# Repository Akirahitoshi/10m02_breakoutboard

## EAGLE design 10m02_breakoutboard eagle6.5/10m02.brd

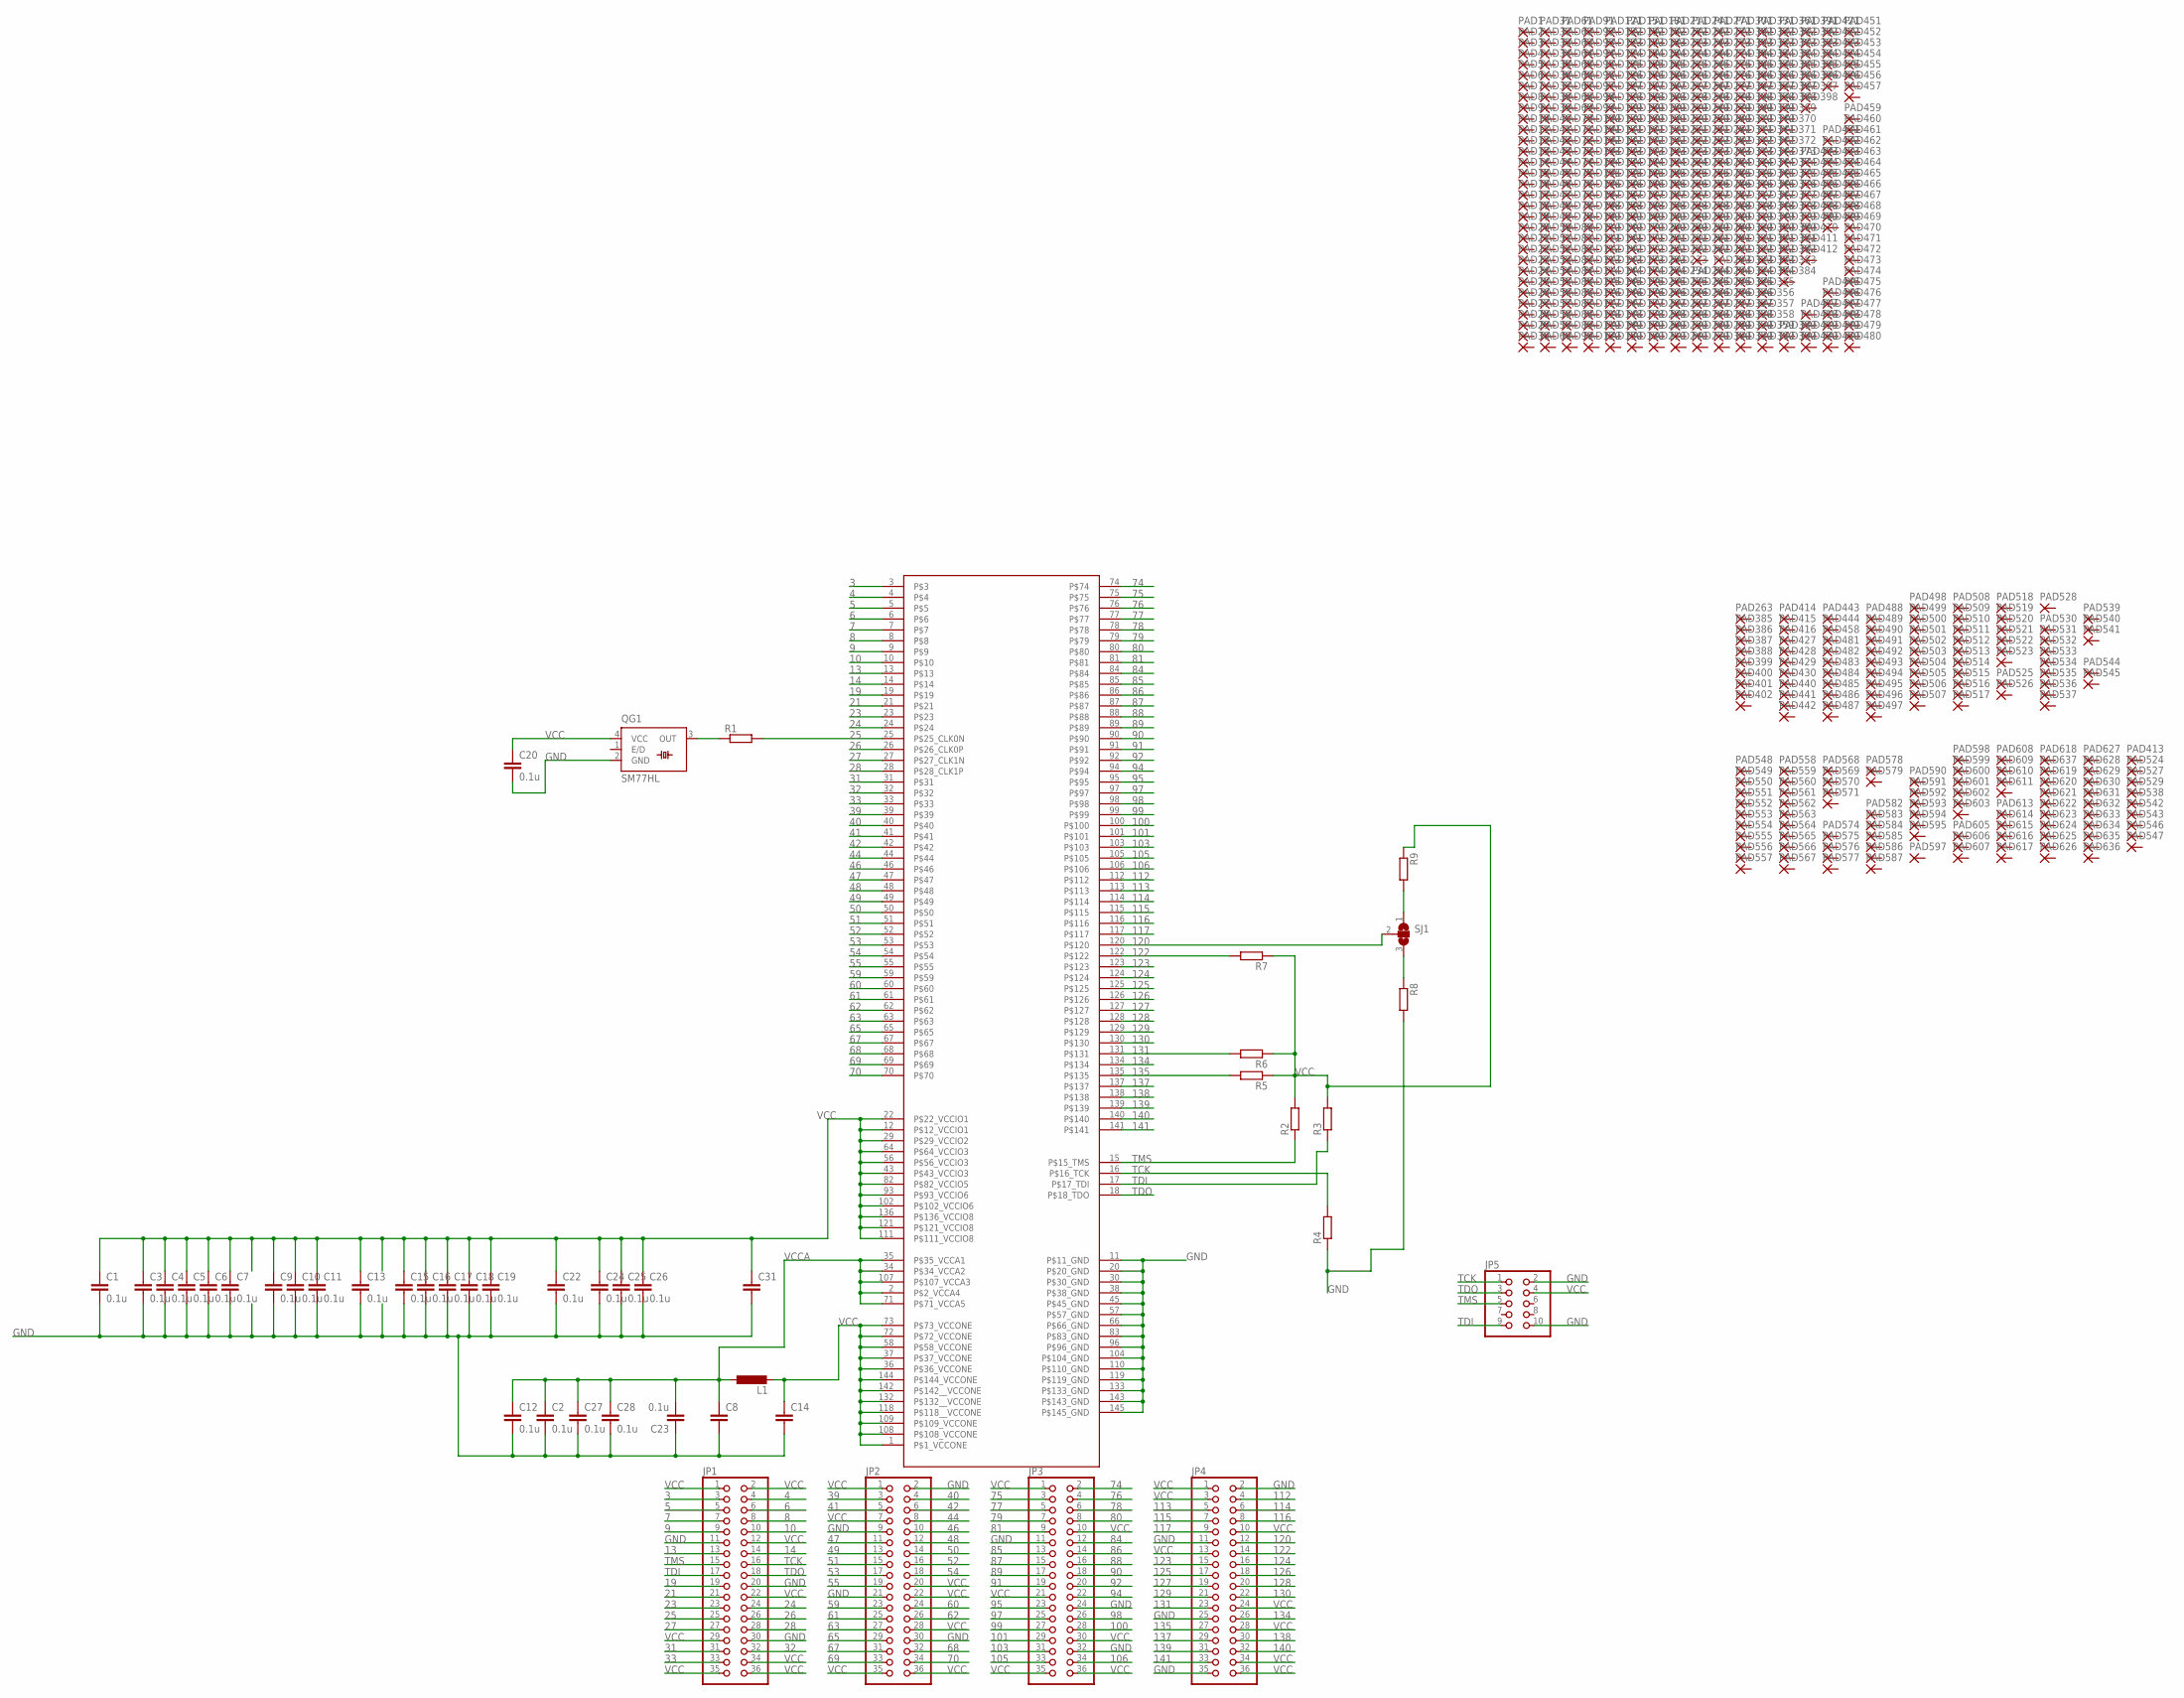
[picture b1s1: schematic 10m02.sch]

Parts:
C1, C2, C3, C4, C5, C6, C7, C9, C10, C11, C12, C13, C15, C16, C17, C18, C19, C20, C22, C23, C24, C25, C26, C27, C28: 0.1u; C0603K
C8, C14: C-EUC3216; C3216
C31: C-EUC3225; C3225
IC1: 10M02SC144; TQFP144G
JP1, JP2, JP3, JP4: PINHD-2X18; 2X18
JP5: PINHD-2X5; 2X05
L1: L-EUL3216C; L3216C
PAD1, PAD2, PAD3, PAD4, PAD5, PAD6, PAD7, PAD8, PAD9, PAD10, PAD11, PAD12, PAD13, PAD14, PAD15, PAD16, PAD17, PAD18, PAD19, PAD20, PAD21, PAD22, PAD23, PAD24, PAD25, PAD26, PAD27, PAD28, PAD29, PAD30, PAD31, PAD32, PAD33, PAD34, PAD35, PAD36, PAD37, PAD38, PAD39, PAD40, PAD41, PAD42, PAD43, PAD44, PAD45, PAD46, PAD47, PAD48, PAD49, PAD50, PAD51, PAD52, PAD53, PAD54, PAD55, PAD56, PAD57, PAD58, PAD59, PAD60, PAD61, PAD62, PAD63, PAD64, PAD65, PAD66, PAD67, PAD68, PAD69, PAD70, PAD71, PAD72, PAD73, PAD74, PAD75, PAD76, PAD77, PAD78, PAD79, PAD80, PAD81, PAD82, PAD83, PAD84, PAD85, PAD86, PAD87, PAD88, PAD89, PAD90, PAD91, PAD92, PAD93, PAD94, PAD95, PAD96, PAD97, PAD98, PAD99, PAD100, PAD101, PAD102, PAD103, PAD104, PAD105, PAD106, PAD107, PAD108, PAD109, PAD110, PAD111, PAD112, PAD113, PAD114, PAD115, PAD116, PAD117, PAD118, PAD119, PAD120, PAD121, PAD122, PAD123, PAD124, PAD125, PAD126, PAD127, PAD128, PAD129, PAD130, PAD131, PAD132, PAD133, PAD134, PAD135, PAD136, PAD137, PAD138, PAD139, PAD140, PAD141, PAD142, PAD143, PAD144, PAD145, PAD146, PAD147, PAD148, PAD149, PAD150, PAD151, PAD152, PAD153, PAD154, PAD155, PAD156, PAD157, PAD158, PAD159, PAD160, PAD161, PAD162, PAD163, PAD164, PAD165, PAD166, PAD167, PAD168, PAD169, PAD170, PAD171, PAD172, PAD173, PAD174, PAD175, PAD176, PAD177, PAD178, PAD179, PAD180, PAD181, PAD182, PAD183, PAD184, PAD185, PAD186, PAD187, PAD188, PAD189, PAD190, PAD191, PAD192, PAD193, PAD194, PAD195, PAD196, PAD197, PAD198, PAD199, PAD200, PAD201, PAD202, PAD203, PAD204, PAD205, PAD206, PAD207, PAD208, PAD209, PAD210, PAD211, PAD212, PAD213, PAD214, PAD215, PAD216, PAD217, PAD218, PAD219, PAD220, PAD221, PAD222, PAD223, PAD224, PAD225, PAD226, PAD227, PAD228, PAD229, PAD230, PAD231, PAD232, PAD233, PAD234, PAD235, PAD236, PAD237, PAD238, PAD239, PAD240, PAD241, PAD242, PAD243, PAD244, PAD245, PAD246, PAD247, PAD248, PAD249, PAD250, PAD251, PAD252, PAD253, PAD254, PAD255, PAD256, PAD257, PAD258, PAD259, PAD260, PAD261, PAD262, PAD264, PAD265, PAD266, PAD267, PAD268, PAD269, PAD270, PAD271, PAD272, PAD273, PAD274, PAD275, PAD276, PAD277, PAD278, PAD279, PAD280, PAD281, PAD282, PAD283, PAD284, PAD285, PAD286, PAD287, PAD288, PAD289, PAD290, PAD291, PAD292, PAD293, PAD294, PAD295, PAD296, PAD297, PAD298, PAD299, PAD300, PAD301, PAD302, PAD303, PAD304, PAD305, PAD306, PAD307, PAD308, PAD309, PAD310, PAD311, PAD312, PAD313, PAD314, PAD315, PAD316, PAD317, PAD318, PAD319, PAD320, PAD321, PAD322, PAD323, PAD324, PAD325, PAD326, PAD327, PAD328, PAD329, PAD330, PAD331, PAD332, PAD333, PAD334, PAD335, PAD336, PAD337, PAD338, PAD339, PAD340, PAD341, PAD342, PAD343, PAD344, PAD345, PAD346, PAD347, PAD348, PAD349, PAD350, PAD351, PAD352, PAD353, PAD354, PAD355, PAD356, PAD357, PAD358, PAD359, PAD360, PAD361, PAD362, PAD363, PAD364, PAD365, PAD366, PAD367, PAD368, PAD369, PAD370, PAD371, PAD372, PAD373, PAD374, PAD375, PAD376, PAD377, PAD378, PAD379, PAD380, PAD381, PAD382, PAD383, PAD384, PAD389, PAD390, PAD391, PAD392, PAD393, PAD394, PAD395, PAD396, PAD397, PAD398, PAD403, PAD404, PAD405, PAD406, PAD407, PAD408, PAD409, PAD410, PAD411, PAD412, PAD417, PAD418, PAD419, PAD420, PAD421, PAD422, PAD423, PAD424, PAD425, PAD426, PAD431, PAD432, PAD433, PAD434, PAD435, PAD436, PAD437, PAD438, PAD439, PAD445, PAD446, PAD447, PAD448, PAD449, PAD450, PAD451, PAD452, PAD453, PAD454, PAD455, PAD456, PAD457, PAD459, PAD460, PAD461, PAD462, PAD463, PAD464, PAD465, PAD466, PAD467, PAD468, PAD469, PAD470, PAD471, PAD472, PAD473, PAD474, PAD475, PAD476, PAD477, PAD478, PAD479, PAD480: 1,6/0,9
PAD263, PAD385, PAD386, PAD387, PAD388, PAD399, PAD400, PAD401, PAD402, PAD413, PAD414, PAD415, PAD416, PAD427, PAD428, PAD429, PAD430, PAD440, PAD441, PAD442, PAD443, PAD444, PAD458, PAD481, PAD482, PAD483, PAD484, PAD485, PAD486, PAD487, PAD488, PAD489, PAD490, PAD491, PAD492, PAD493, PAD494, PAD495, PAD496, PAD497, PAD498, PAD499, PAD500, PAD501, PAD502, PAD503, PAD504, PAD505, PAD506, PAD507, PAD508, PAD509, PAD510, PAD511, PAD512, PAD513, PAD514, PAD515, PAD516, PAD517, PAD518, PAD519, PAD520, PAD521, PAD522, PAD523, PAD524, PAD525, PAD526, PAD527, PAD528, PAD529, PAD530, PAD531, PAD532, PAD533, PAD534, PAD535, PAD536, PAD537, PAD538, PAD539, PAD540, PAD541, PAD542, PAD543, PAD544, PAD545, PAD546, PAD547, PAD548, PAD549, PAD550, PAD551, PAD552, PAD553, PAD554, PAD555, PAD556, PAD557, PAD558, PAD559, PAD560, PAD561, PAD562, PAD563, PAD564, PAD565, PAD566, PAD567, PAD568, PAD569, PAD570, PAD571, PAD574, PAD575, PAD576, PAD577, PAD578, PAD579, PAD582, PAD583, PAD584, PAD585, PAD586, PAD587, PAD590, PAD591, PAD592, PAD593, PAD594, PAD595, PAD597, PAD598, PAD599, PAD600, PAD601, PAD602, PAD603, PAD605, PAD606, PAD607, PAD608, PAD609, PAD610, PAD611, PAD613, PAD614, PAD615, PAD616, PAD617, PAD618, PAD619, PAD620, PAD621, PAD622, PAD623, PAD624, PAD625, PAD626, PAD627, PAD628, PAD629, PAD630, PAD631, PAD632, PAD633, PAD634, PAD635, PAD636, PAD637: SMD2; SMD1,27-2,54
QG1: SM77HL
R1: R-EU_R2012W; R2012W
R2, R3, R4, R5, R6, R7, R8, R9: R-EU_R2012; R2012
SJ1: SJ2W; SJ_2

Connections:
3: IC1.3, JP1.3
4: IC1.4, JP1.4
5: IC1.5, JP1.5
6: IC1.6, JP1.6
7: IC1.7, JP1.7
8: IC1.8, JP1.8
9: IC1.9, JP1.9
10: IC1.10, JP1.10
13: IC1.13, JP1.13
14: IC1.14, JP1.14
19: IC1.19, JP1.19
21: IC1.21, JP1.21
23: IC1.23, JP1.23
24: IC1.24, JP1.24
25: IC1.25 (P$25_CLK0N), JP1.25, R1.2
26: IC1.26 (P$26_CLK0P), JP1.26
27: IC1.27 (P$27_CLK1N), JP1.27
28: IC1.28 (P$28_CLK1P), JP1.28
31: IC1.31, JP1.31
32: IC1.32, JP1.32
33: IC1.33, JP1.33
39: IC1.39, JP2.3
40: IC1.40, JP2.4
41: IC1.41, JP2.5
42: IC1.42, JP2.6
44: IC1.44, JP2.8
46: IC1.46, JP2.10
47: IC1.47, JP2.11
48: IC1.48, JP2.12
49: IC1.49, JP2.13
50: IC1.50, JP2.14
51: IC1.51, JP2.15
52: IC1.52, JP2.16
53: IC1.53, JP2.17
54: IC1.54, JP2.18
55: IC1.55, JP2.19
59: IC1.59, JP2.23
60: IC1.60, JP2.24
61: IC1.61, JP2.25
62: IC1.62, JP2.26
63: IC1.63, JP2.27
65: IC1.65, JP2.29
67: IC1.67, JP2.31
68: IC1.68, JP2.32
69: IC1.69, JP2.33
70: IC1.70, JP2.34
74: IC1.74, JP3.2
75: IC1.75, JP3.3
76: IC1.76, JP3.4
77: IC1.77, JP3.5
78: IC1.78, JP3.6
79: IC1.79, JP3.7
80: IC1.80, JP3.8
81: IC1.81, JP3.9
84: IC1.84, JP3.12
85: IC1.85, JP3.13
86: IC1.86, JP3.14
87: IC1.87, JP3.15
88: IC1.88, JP3.16
89: IC1.89, JP3.17
90: IC1.90, JP3.18
91: IC1.91, JP3.19
92: IC1.92, JP3.20
94: IC1.94, JP3.22
95: IC1.95, JP3.23
97: IC1.97, JP3.25
98: IC1.98, JP3.26
99: IC1.99, JP3.27
100: IC1.100, JP3.28
101: IC1.101, JP3.29
103: IC1.103, JP3.31
105: IC1.105, JP3.33
106: IC1.106, JP3.34
112: IC1.112, JP4.4
113: IC1.113, JP4.5
114: IC1.114, JP4.6
115: IC1.115, JP4.7
116: IC1.116, JP4.8
117: IC1.117, JP4.9
120: IC1.120, JP4.12, SJ1.2
122: IC1.122, JP4.14, R7.2
123: IC1.123, JP4.15
124: IC1.124, JP4.16
125: IC1.125, JP4.17
126: IC1.126, JP4.18
127: IC1.127, JP4.19
128: IC1.128, JP4.20
129: IC1.129, JP4.21
130: IC1.130, JP4.22
131: IC1.131, JP4.23, R6.2
134: IC1.134, JP4.26
135: IC1.135, JP4.27, R5.2
137: IC1.137, JP4.29
138: IC1.138, JP4.30
139: IC1.139, JP4.31
140: IC1.140, JP4.32
141: IC1.141, JP4.33
GND: C1.2, C2.2, C3.2, C4.2, C5.2, C6.2, C7.2, C8.2, C9.2, C10.2, C11.2, C12.2, C13.2, C14.2, C15.2, C16.2, C17.2, C18.2, C19.2, C20.2, C22.2, C23.1, C24.2, C25.2, C26.2, C27.2, C28.2, C31.2, IC1.11 (P$11_GND), IC1.20 (P$20_GND), IC1.30 (P$30_GND), IC1.38 (P$38_GND), IC1.45 (P$45_GND), IC1.57 (P$57_GND), IC1.66 (P$66_GND), IC1.83 (P$83_GND), IC1.96 (P$96_GND), IC1.104 (P$104_GND), IC1.110 (P$110_GND), IC1.119 (P$119_GND), IC1.133 (P$133_GND), IC1.143 (P$143_GND), IC1.145 (P$145_GND), JP1.11, JP1.20, JP1.30, JP2.2, JP2.9, JP2.21, JP2.30, JP3.11, JP3.24, JP3.32, JP4.2, JP4.11, JP4.25, JP4.35, JP5.2, JP5.10, QG1.2 (GND), R4.1, R8.2
unnamed: QG1.3 (OUT), R1.1
unnamed: R9.2, SJ1.1
unnamed: R8.1, SJ1.3
TCK: IC1.16 (P$16_TCK), JP1.16, JP5.1, R4.2
TDI: IC1.17 (P$17_TDI), JP1.17, JP5.9, R3.1
TDO: IC1.18 (P$18_TDO), JP1.18, JP5.3
TMS: IC1.15 (P$15_TMS), JP1.15, JP5.5, R2.1
VCC: C1.1, C3.1, C4.1, C5.1, C6.1, C7.1, C9.1, C10.1, C11.1, C13.1, C14.1, C15.1, C16.1, C17.1, C18.1, C19.1, C20.1, C22.1, C24.1, C25.1, C26.1, C31.1, IC1.1 (P$1_VCCONE), IC1.12 (P$12_VCCIO1), IC1.22 (P$22_VCCIO1), IC1.29 (P$29_VCCIO2), IC1.36 (P$36_VCCONE), IC1.37 (P$37_VCCONE), IC1.43 (P$43_VCCIO3), IC1.56 (P$56_VCCIO3), IC1.58 (P$58_VCCONE), IC1.64 (P$64_VCCIO3), IC1.72 (P$72_VCCONE), IC1.73 (P$73_VCCONE), IC1.82 (P$82_VCCIO5), IC1.93 (P$93_VCCIO6), IC1.102 (P$102_VCCIO6), IC1.108 (P$108_VCCONE), IC1.109 (P$109_VCCONE), IC1.111 (P$111_VCCIO8), IC1.118 (P$118__VCCONE), IC1.121 (P$121_VCCIO8), IC1.132 (P$132__VCCONE), IC1.136 (P$136_VCCIO8), IC1.142 (P$142__VCCONE), IC1.144 (P$144_VCCONE), JP1.1, JP1.2, JP1.12, JP1.22, JP1.29, JP1.34, JP1.35, JP1.36, JP2.1, JP2.7, JP2.20, JP2.22, JP2.28, JP2.35, JP2.36, JP3.1, JP3.10, JP3.21, JP3.30, JP3.35, JP3.36, JP4.1, JP4.3, JP4.10, JP4.13, JP4.24, JP4.28, JP4.34, JP4.36, JP5.4, L1.2, QG1.4 (VCC), R2.2, R3.2, R5.1, R6.1, R7.1, R9.1
VCCA: C2.1, C8.1, C12.1, C23.2, C27.1, C28.1, IC1.2 (P$2_VCCA4), IC1.34 (P$34_VCCA2), IC1.35 (P$35_VCCA1), IC1.71 (P$71_VCCA5), IC1.107 (P$107_VCCA3), L1.1

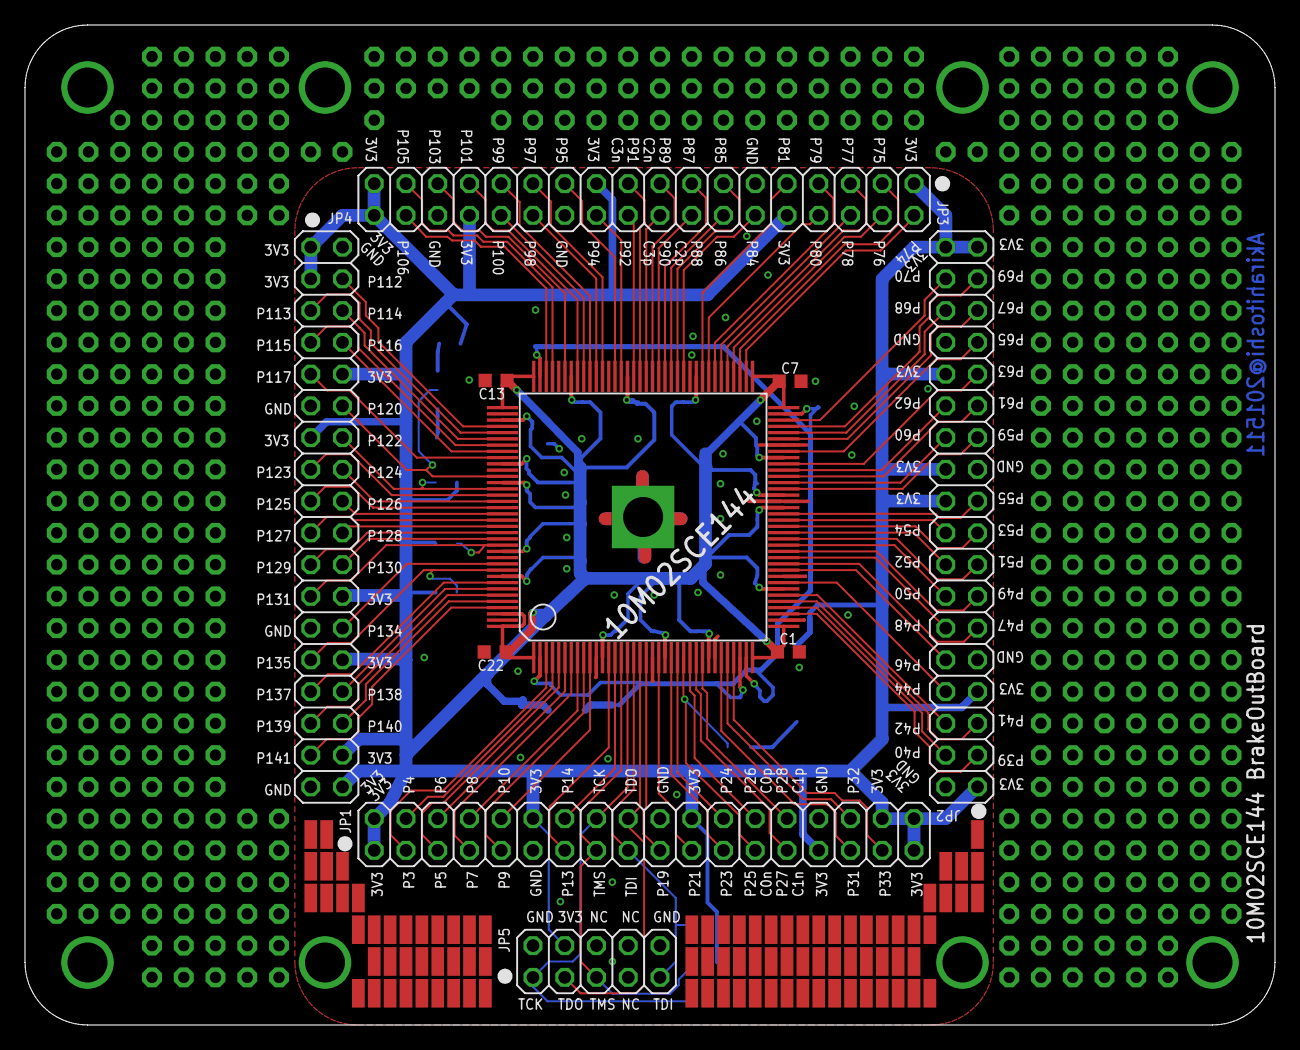
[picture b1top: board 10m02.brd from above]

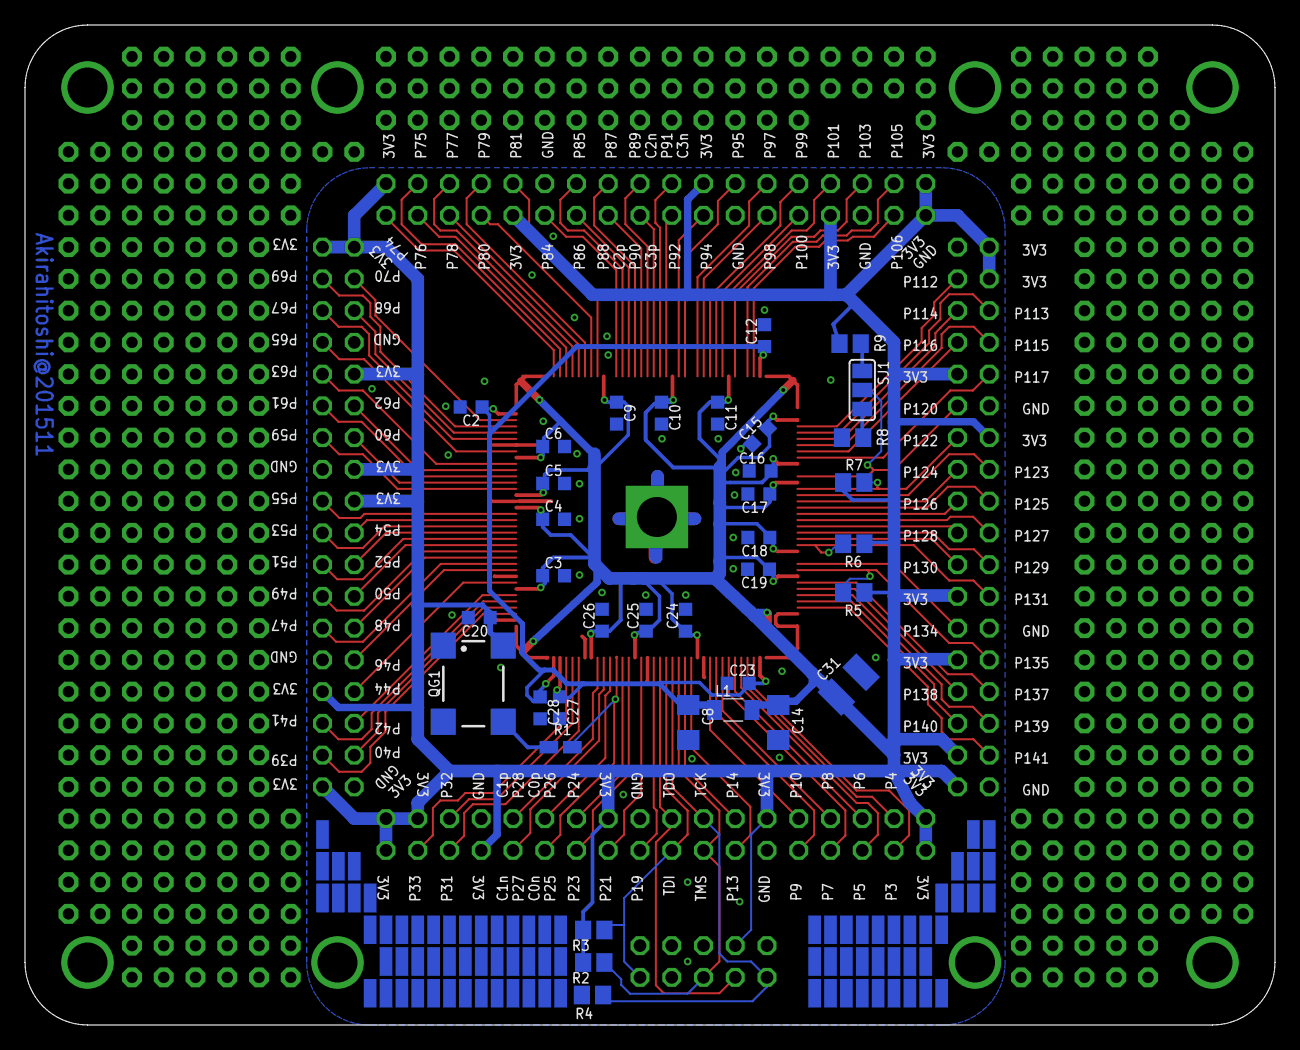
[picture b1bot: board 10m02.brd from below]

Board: 2 copper layers, 100.0 x 80.0 mm, 674 parts (117 on the bottom side), 107 nets.

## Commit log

2016-07-08 :boom::camel: Added .gitattributes & .gitignore files
2016-07-08 10m02 brakeoutboard
    eagle6.5file
